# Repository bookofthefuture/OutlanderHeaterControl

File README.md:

# OutlanderHeaterControl
Arduino sketch for an Arduino with an MCP2515 to control a Mitsubishi Outlander PHEV Gen3 (2016+) water heater based on Jamie Jones's original. Tweaking to add on/off switch integrated into pot and potentially remote control via Home Assistant node down the line.

Heater control itself is now handled by [Zombieverter](https://openinverter.org/wiki/Zombieverter), rather than this
controller talking to the heater directly. On CAN ID 509 (0x1FD), this controller sends a single message with:
- Byte 0: HeatReq, `0x01` if the pot's switch is on, `0x00` otherwise
- Bytes 1-2: the pot value mapped to 0-4095, little-endian

Zombieverter's CAN input map needs to be configured to match this layout.

This is now the only CAN message this controller sends - it no longer generates a BMS heartbeat (0x285) or
rebroadcasts heater/HV status telemetry (0x300).

See https://openinverter.org/wiki/Mitsubishi_Outlander_Water_Heater

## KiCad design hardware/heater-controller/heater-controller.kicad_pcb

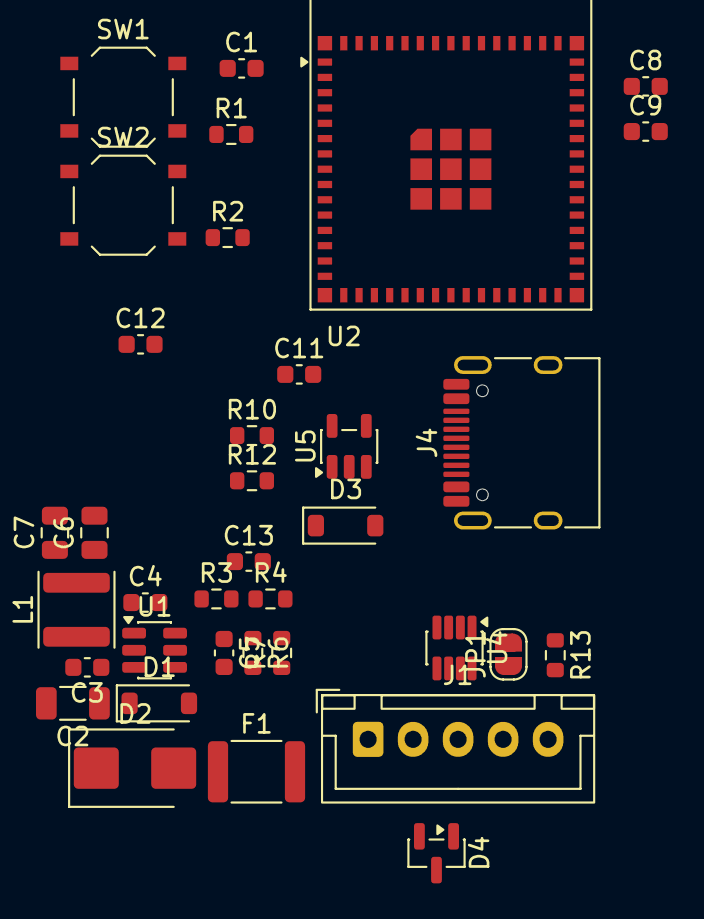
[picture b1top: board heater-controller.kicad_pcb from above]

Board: 2 copper layers, 36 parts (0 on the bottom side), 22 nets, no tracks yet.

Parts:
C1, C11, C13: 1uF; C_0603_1608Metric
C2: 10uF 35V; C_1206_3216Metric
C3: 100nF 50V; C_0603_1608Metric
C4, C9, C12: 100nF; C_0603_1608Metric
C5: 56pF; C_0603_1608Metric
C6, C7: 22uF; C_0805_2012Metric
C8: 10uF; C_0603_1608Metric
D1, D3: B5819W; D_SOD-123
D2: SMBJ18CA; D_SMB
D4: NUP2105L; SOT-23
F1: 500mA; Fuse_1812_4532Metric
J1: JST-XH 5P; JST_XH_B5B-XH-A_1x05_P2.50mm_Vertical
J4: USB_C_Receptacle_USB2.0_14P; USB_C_Receptacle_HRO_TYPE-C-31-M-12
JP1: SolderJumper_2_Open; SolderJumper-2_P1.3mm_Open_RoundedPad1.0x1.5mm
L1: 10uH; L_Changjiang_FNR4020S
R1, R2: 10k; R_0603_1608Metric
R3: 422k; R_0603_1608Metric
R4: 63.4k; R_0603_1608Metric
R6: 100k; R_0603_1608Metric
R7: 22.1k; R_0603_1608Metric
R10, R12: 5.1k; R_0603_1608Metric
R13: 120; R_0603_1608Metric
SW1, SW2: SW_Push; SW_Push_1P1T_XKB_TS-1187A
U1: TPS54202DDC; SOT-23-6
U2: ESP32-S3-MINI-1-N8R2; ESP32-S2-MINI-1
U4: TCAN332; SOT-23-8
U5: AP2112K-3.3; SOT-23-5

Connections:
+3.3V: C5.1, C6.1, C7.1, C8.1, C9.1, C12.1, C13.1, L1.2, R1.1, R2.1, R6.1, U2.3 (3V3), U4.3 (VCC), U5.5 (VOUT)
/12V_RAW: D1.2 (A), D2.2 (A2), F1.1
/BOOT_CIRC: R2.2, SW2.2, U2.4 (IO0)
/CAN_H: D4.1 (K), J1.3, R13.2, U4.7 (CANH)
/CAN_L: D4.2 (K), J1.2, JP1.1 (A), U4.6 (CANL)
/CAN_RX: U2.10 (IO6), U4.4 (RXD)
/CAN_TX: U2.9 (IO5), U4.1 (TXD)
/DN: J4.A7 (D-), J4.B7 (D-), U2.23 (USB_D-)
/DP: J4.A6 (D+), J4.B6 (D+), U2.24 (USB_D+)
/RES_CIRC: C1.1, R1.2, SW1.2, U2.45 (EN)
/VIN_12V: C2.1, C3.1, D1.1 (K), R3.1, U1.3 (VIN)
GND: C1.2, C2.2, C3.2, C6.2, C7.2, C8.2, C9.2, C11.2, C12.2, C13.2, D2.1 (A1), D4.3 (A), J1.4, J4.A1 (GND), J4.A12 (GND), J4.B1 (GND), J4.B12 (GND), J4.SH (SHIELD), R4.2, R7.2, R10.2, R12.2, SW1.1, SW2.1, U1.1 (GND), U2.1 (GND), U2.2 (GND), U2.42 (GND), U2.43 (GND), U2.46 (GND), U2.47 (GND), U2.48 (GND), U2.49 (GND), U2.50 (GND), U2.51 (GND), U2.52 (GND), U2.53 (GND), U2.54 (GND), U2.55 (GND), U2.56 (GND), U2.57 (GND), U2.58 (GND), U2.59 (GND), U2.60 (GND), U2.61 (GND), U2.62 (GND), U2.63 (GND), U2.64 (GND), U2.65 (GND), U4.2 (GND), U5.2 (GND)
unnamed: D3.2 (A), J4.A4 (VBUS), J4.A9 (VBUS), J4.B4 (VBUS), J4.B9 (VBUS)
unnamed: C11.1, D3.1 (K), U5.1 (VIN), U5.3 (EN)
unnamed: F1.2, J1.1
unnamed: J4.A5 (CC1), R12.1
unnamed: J4.B5 (CC2), R10.1
unnamed: JP1.2 (B), R13.1
unnamed: C4.2, U1.6 (BOOT)
unnamed: R3.2, R4.1, U1.5 (EN)
unnamed: C5.2, R6.2, R7.1, U1.4 (FB)
unnamed: C4.1, L1.1, U1.2 (SW)

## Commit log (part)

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2023-11-14 stripped out screen driver & changed contactor check
    should now check for dc-dc enabled, which in my car means that the contactors are closed. Not using a display in my configuration but will change to post temp data on canbus for display in binnacle
2023-11-22 added can send
    calculated data and packaged to send over can. fixed compilation issues.
2023-11-22 hv check tweaks
    removed the if around the hv check and renamed it, since it's not talking to OI but the charger
2023-12-09 Update OutlanderHeaterControl.ino
    added i/o notes for reference
2024-02-26 commented out unnecessary code
    commented out extra info sending on 0x300
2024-12-14 added missing line for MCP_CAN
2025-02-28 debug and temp tweaks
    wrapped all serial comms in debug ifdefs
    tweaks min and max temps
2025-02-28 tweaked mintemp again
2025-03-02 disable keep alive
    BMS already sending out 0x285. If it's not, then this controller certainly shouldn't be.
2025-03-04 restored canbus data sending for ev gauge
2025-03-07 check for heartbeat from bms and generate if not there
    If you want heating while charging, you can't have two different devices generating the heartbeat. Problem remains that the one generated by the BMS may not enable the heater. But at least now the he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
2025-03-09 inverted power switch
